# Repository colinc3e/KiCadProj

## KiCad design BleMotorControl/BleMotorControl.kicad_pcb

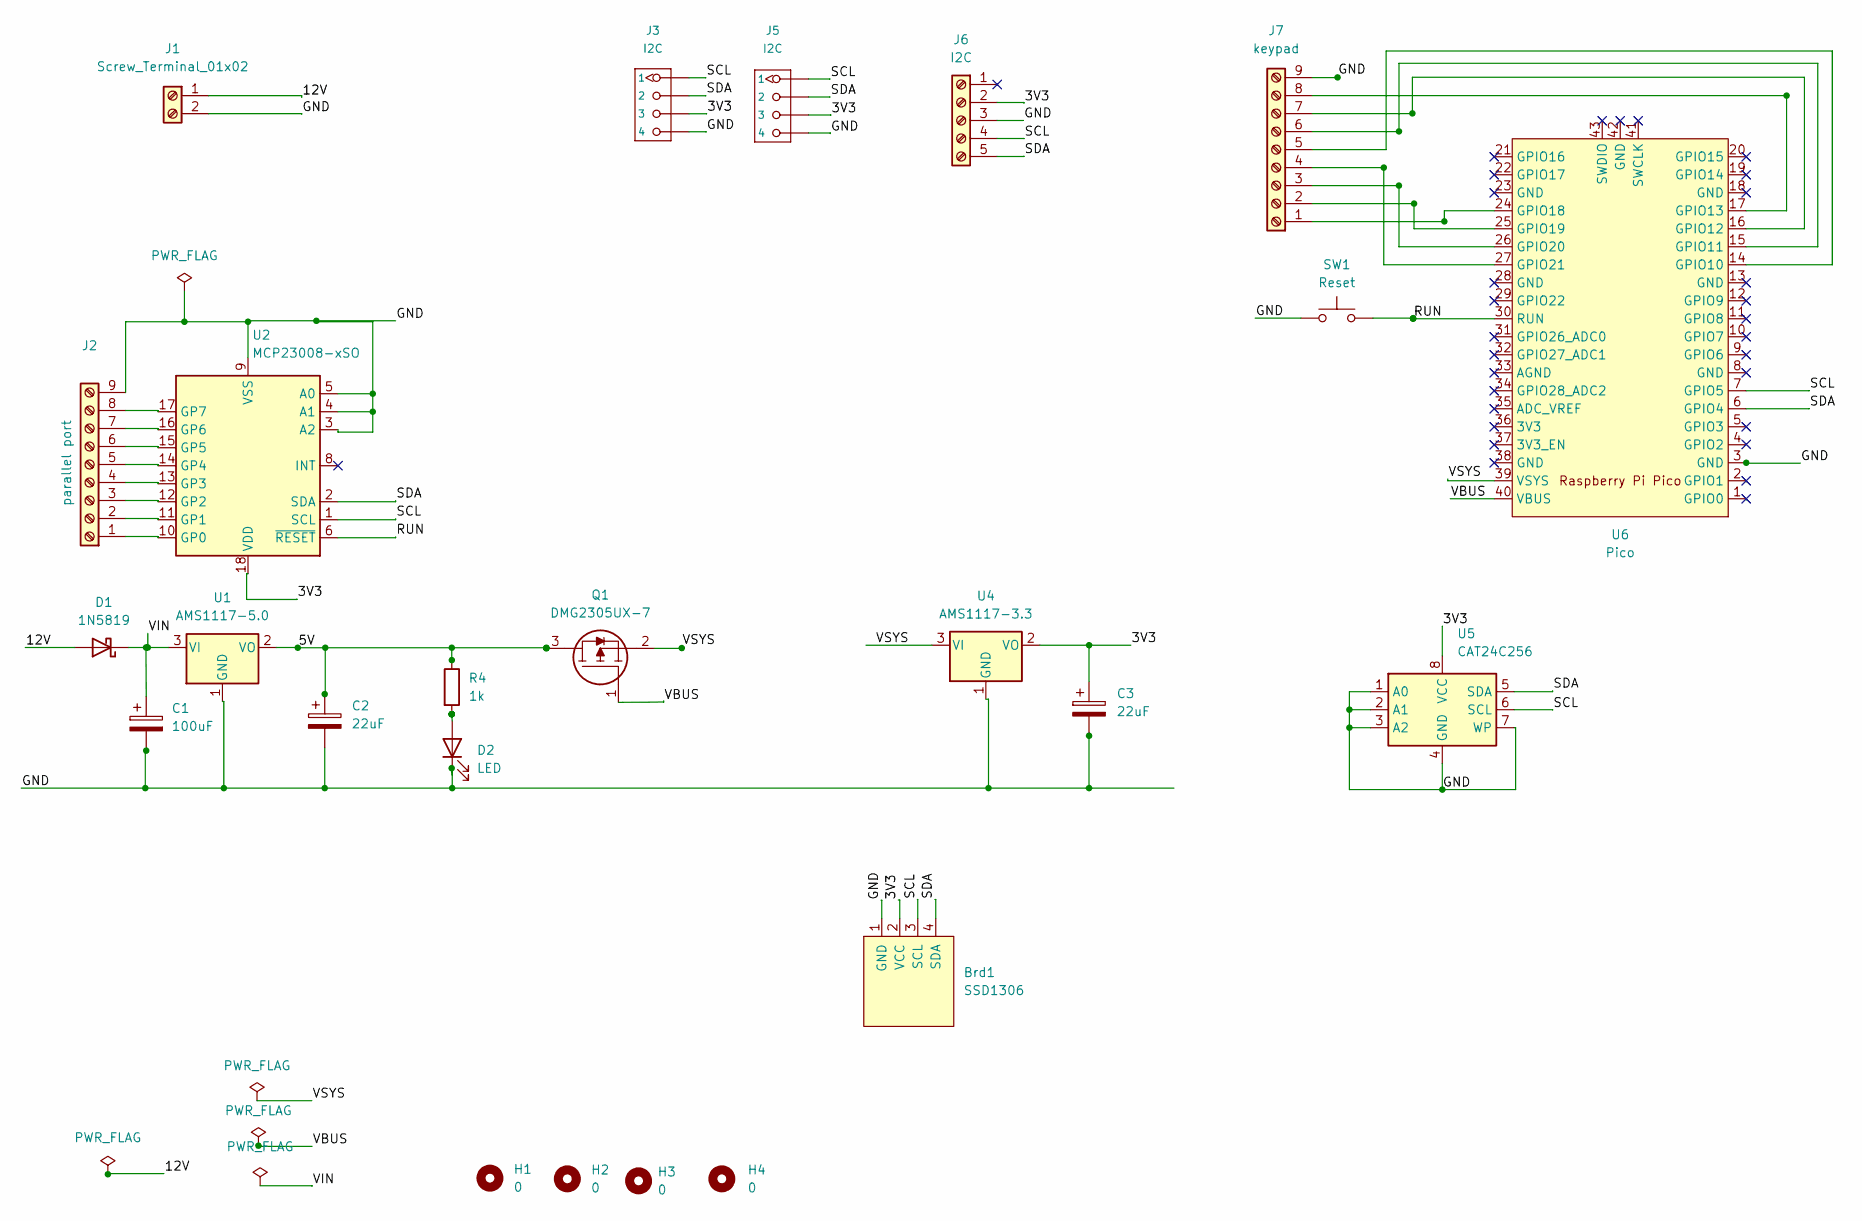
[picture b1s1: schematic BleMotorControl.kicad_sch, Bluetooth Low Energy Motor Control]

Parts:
Brd1: SSD1306; 128x64OLED
C1: 100uF; CP_Radial_Tantal_D8.0mm_P5.00mm
C2, C3: 22uF; CP_Radial_Tantal_D8.0mm_P5.00mm
D1: 1N5819; D_DO-41_SOD81_P10.16mm_Horizontal
D2: LED; LED_D3.0mm
H1, H2, H3, H4: 0; MountingHole_3.2mm_M3
J1: Screw_Terminal_01x02; TerminalBlock_Phoenix_PT-1,5-2-3.5-H_1x02_P3.50mm_Horizontal
J2: parallel port; PinHeader_1x09_P2.54mm_Vertical
J3, J5: I2C; HW4-2.0
J6: I2C; PinHeader_1x05_P2.54mm_Vertical
J7: keypad; PinHeader_1x09_P2.54mm_Vertical
Q1: DMG2305UX-7; SOT-23-3; Mouser Part Number 621-DMG2305UX-7
R4: 1k; R_1206_3216Metric
SW1: Reset; SW_Tactile_SPST_NO_Straight_CK_PTS636Sx25SMTRLFS
U1: AMS1117-5.0; SOT-223-3_TabPin2
U2: MCP23008-xSO; SOIC-18W_7.5x11.6mm_P1.27mm
U4: AMS1117-3.3; SOT-223-3_TabPin2
U5: CAT24C256; DIP-8_W7.62mm_LongPads
U6: Pico; RP2040Pico

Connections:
/3V3: Brd1.2 (VCC), C3.1, J3.3, J5.3, J6.2, U2.18 (VDD), U4.2 (VO), U5.8 (VCC)
/5V: C2.1, Q1.3, R4.1, U1.2 (VO)
/12V: D1.2 (A), J1.1
/GND: Brd1.1 (GND), C1.2, C2.2, C3.2, D2.1 (K), J1.2, J2.9, J3.4, J5.4, J6.3, J7.9, SW1.1, U1.1 (GND), U2.3 (A2), U2.4 (A1), U2.5 (A0), U2.9 (VSS), U4.1 (GND), U5.1 (A0), U5.2 (A1), U5.3 (A2), U5.4 (GND), U5.7 (WP), U6.3 (GND)
/RUN: SW1.2, U2.6 (~RESET), U6.30 (RUN)
/SCL: Brd1.3 (SCL), J3.1, J5.1, J6.4, U2.1 (SCL), U5.6 (SCL), U6.7 (GPIO5)
/SDA: Brd1.4 (SDA), J3.2, J5.2, J6.5, U2.2 (SDA), U5.5 (SDA), U6.6 (GPIO4)
/VBUS: Q1.1, U6.40 (VBUS)
/VIN: C1.1, D1.1 (K), U1.3 (VI)
/VSYS: Q1.2, U4.3 (VI), U6.39 (VSYS)
unnamed: D2.2 (A), R4.2
unnamed: J2.1, U2.10 (GP0)
unnamed: J2.2, U2.11 (GP1)
unnamed: J2.3, U2.12 (GP2)
unnamed: J2.4, U2.13 (GP3)
unnamed: J2.5, U2.14 (GP4)
unnamed: J2.6, U2.15 (GP5)
unnamed: J2.7, U2.16 (GP6)
unnamed: J2.8, U2.17 (GP7)
unnamed: J7.1, U6.24 (GPIO18)
unnamed: J7.2, U6.25 (GPIO19)
unnamed: J7.3, U6.26 (GPIO20)
unnamed: J7.4, U6.27 (GPIO21)
unnamed: J7.5, U6.14 (GPIO10)
unnamed: J7.6, U6.15 (GPIO11)
unnamed: J7.7, U6.16 (GPIO12)
unnamed: J7.8, U6.17 (GPIO13)

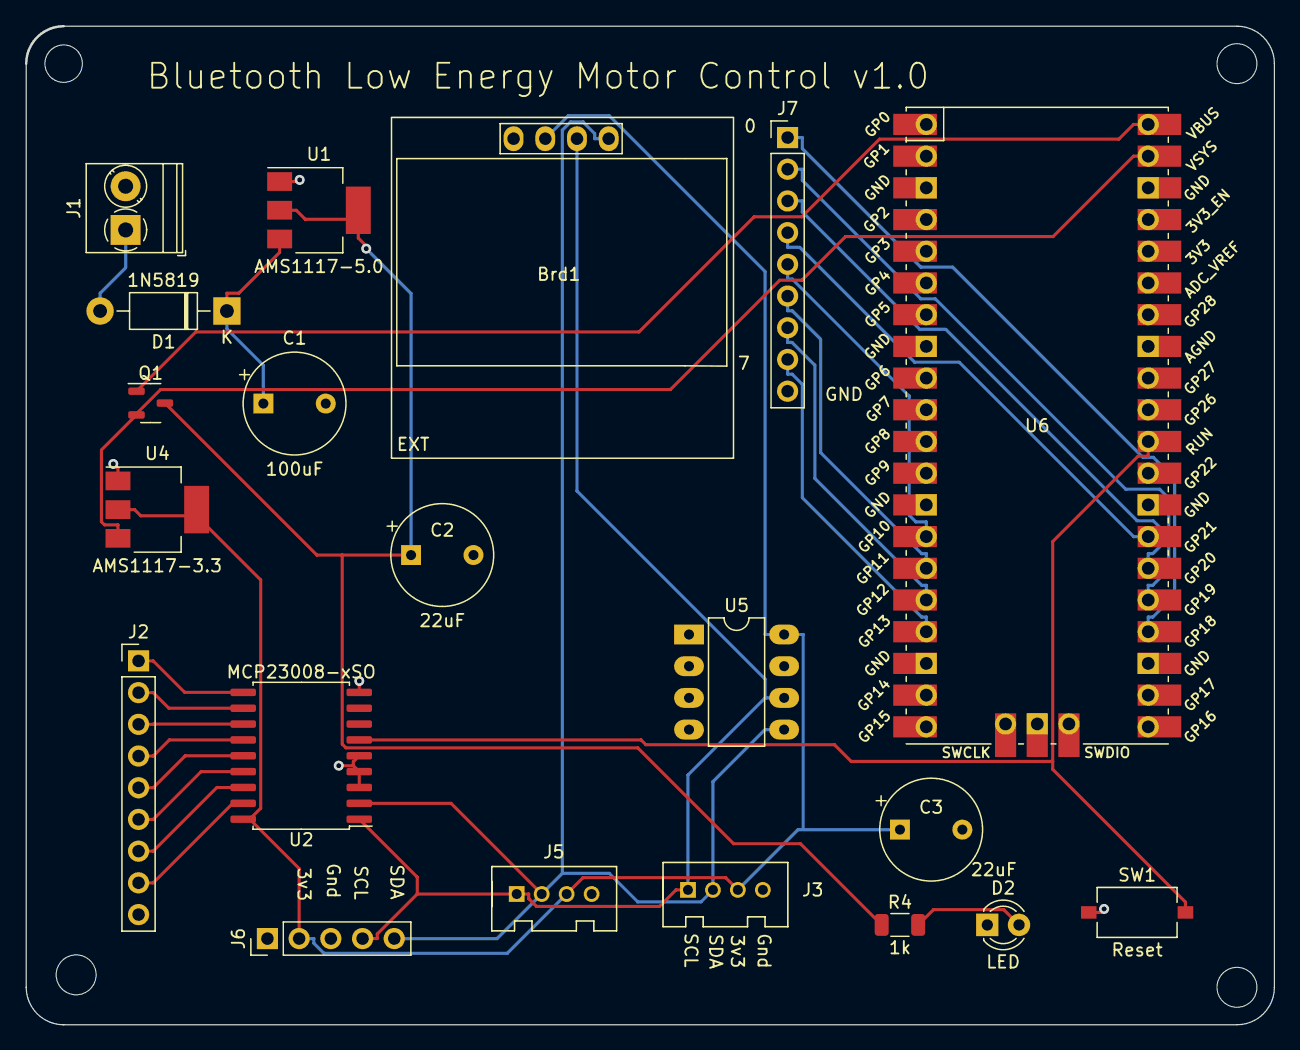
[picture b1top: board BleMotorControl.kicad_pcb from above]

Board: 2 copper layers, 100.0 x 80.0 mm, 24 parts (0 on the bottom side), 27 nets.

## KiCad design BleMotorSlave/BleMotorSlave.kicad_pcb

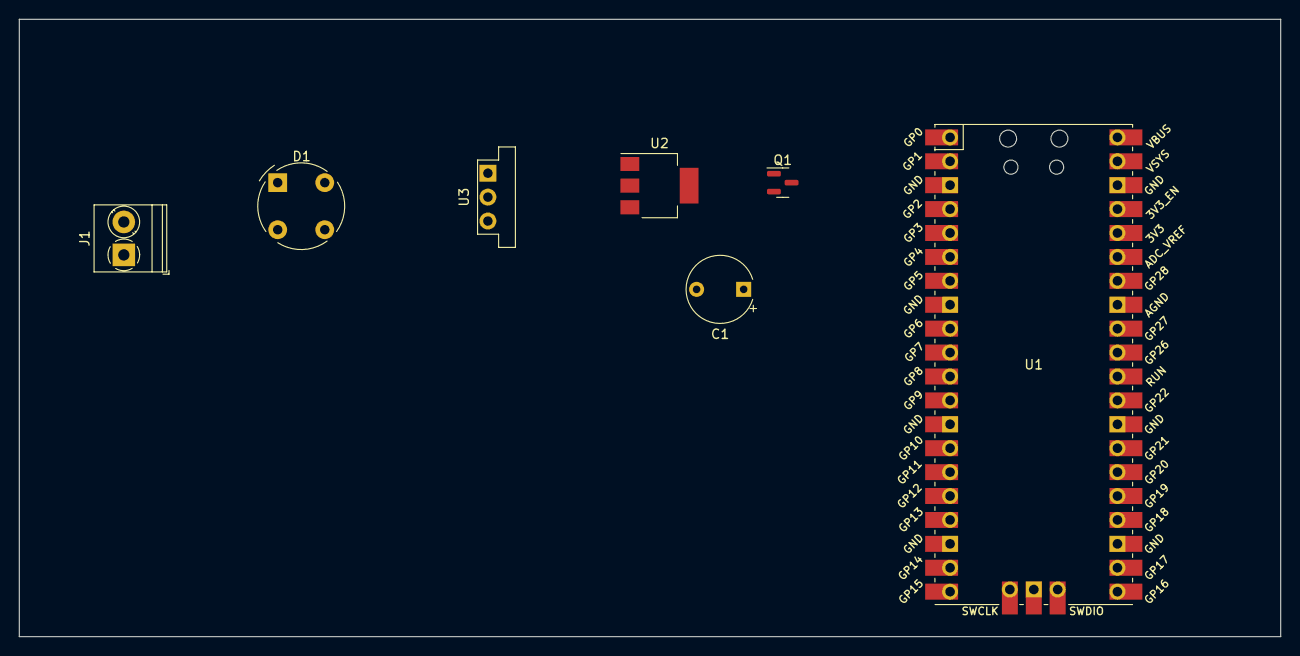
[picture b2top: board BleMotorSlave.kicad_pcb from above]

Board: 2 copper layers, 134.0 x 65.6 mm, 7 parts (0 on the bottom side), 8 nets, no tracks yet.

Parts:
C1: 22uF; CP_Radial_Tantal_D7.0mm_P5.00mm
D1: RB151; Diode_Bridge_Round_D9.0mm
J1: Screw_Terminal_01x02; TerminalBlock_Phoenix_PT-1,5-2-3.5-H_1x02_P3.50mm_Horizontal
Q1: DMG2305UX-7; SOT-23
U1: Pico; RPi_Pico_SMD_TH
U2: AMS1117-5.0; SOT-223-3_TabPin2
U3: OKI-78SR-12_1.0-W36-C; Converter_DCDC_Murata_OKI-78SR_Vertical

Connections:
/5V: C1.1, Q1.3, U2.2 (VO)
GND: C1.2, D1.3 (-), U2.1 (GND), U3.2 (GND)
unnamed: D1.1 (+), U3.1 (IN)
unnamed: D1.2, J1.2
unnamed: D1.4, J1.1
unnamed: Q1.1, U1.40 (VBUS)
unnamed: Q1.2, U1.39 (VSYS)
unnamed: U2.3 (VI), U3.3 (OUT)

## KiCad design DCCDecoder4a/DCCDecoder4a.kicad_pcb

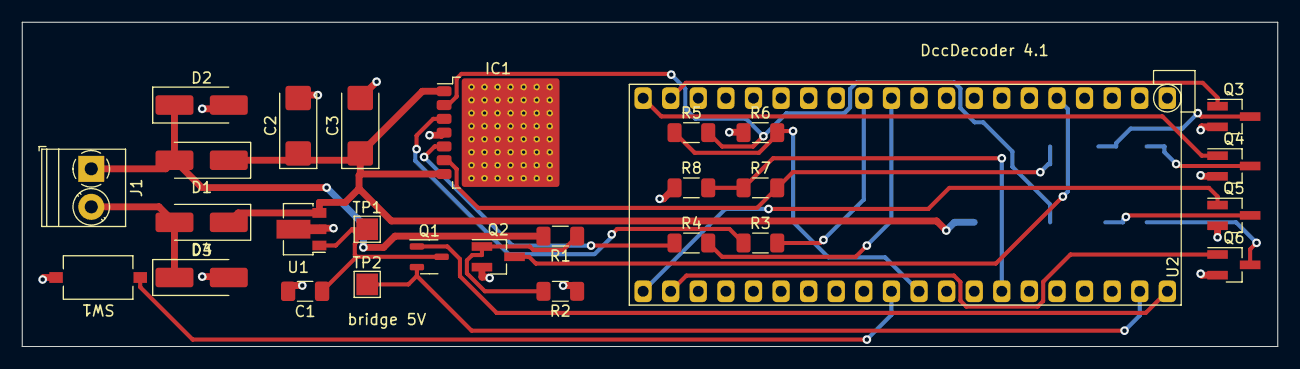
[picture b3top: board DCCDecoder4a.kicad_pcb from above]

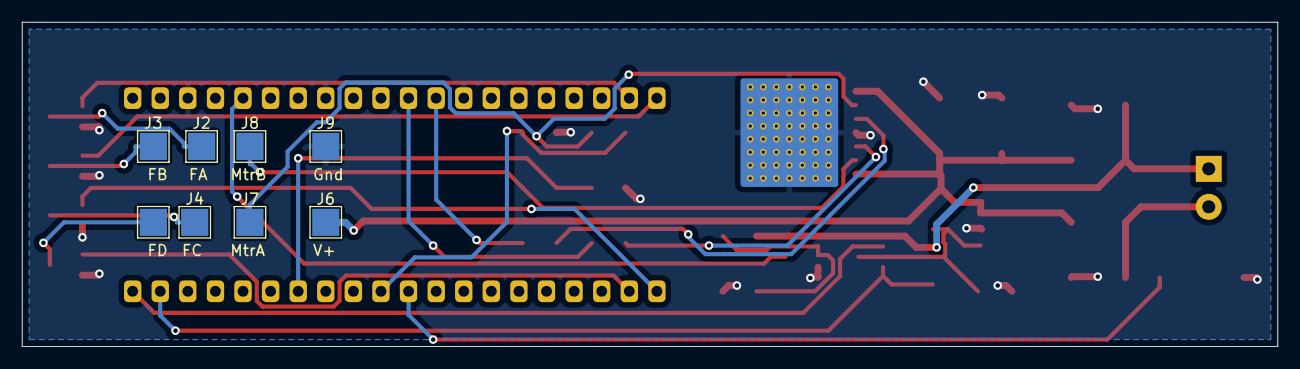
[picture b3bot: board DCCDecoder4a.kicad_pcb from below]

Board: 2 copper layers, 115.6 x 29.8 mm, 36 parts (8 on the bottom side), 26 nets.

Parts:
C1: 10uf/16V; C_1206_3216Metric_Pad1.33x1.80mm_HandSolder
C2: 10uF/25V; CP_EIA-6032-20_AVX-F_Pad2.25x2.35mm_HandSolder
C3: 10uF/25v; CP_EIA-6032-20_AVX-F_Pad2.25x2.35mm_HandSolder
D1, D2, D3, D4: RBR3L60AD; D_SMA_Handsoldering
IC1: BD62321HFP-TR; Rohm_HRP7
J1: Screw_Terminal_01x02; TerminalBlock_Phoenix_PT-1,5-2-3.5-H_1x02_P3.50mm_Horizontal
J2: 0; TestPoint_Pad_2.5x2.5mm
J3: 1; TestPoint_Pad_2.5x2.5mm
J4: 2; TestPoint_Pad_2.5x2.5mm
J5: 3; TestPoint_Pad_2.5x2.5mm
J6: +V; TestPoint_Pad_2.5x2.5mm
J7: M_OUT_B; TestPoint_Pad_2.5x2.5mm
J8: M_OUT_A; TestPoint_Pad_2.5x2.5mm
J9: GND; TestPoint_Pad_2.5x2.5mm
Q1: DMG2305UX-7; SOT-23-3
Q2, Q3, Q4, Q5, Q6: 2N7002BK; SOT-23_Handsoldering
R1, R2, R5, R7: 6k8; R_1206_3216Metric_Pad1.30x1.75mm_HandSolder
R3, R4: 10k; R_1206_3216Metric_Pad1.30x1.75mm_HandSolder
R6, R8: 1k; R_1206_3216Metric_Pad1.30x1.75mm_HandSolder
SW1: SW_Push; SW_Tactile_SPST_NO_Straight_CK_PTS636Sx25SMTRLFS
TP1, TP2: TestPoint; TestPoint_Pad_2.0x2.0mm
U1: AP7384-50Y; SOT-89-3
U2: Pico_RaspberryPico; RaspberryPico_TH_NoSWD

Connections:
+5V: C1.1, Q1.3, TP1.1, U1.1 (VO)
+V: C2.1, C3.1, D1.1 (K), D4.1 (K), IC1.1 (VCC_1), IC1.7 (VCC_2), J6.1, U1.3 (VI)
/ADC_EMF_A: R5.1, R6.2, U2.31 (GPIO26)
/DCC1: D1.2 (A), D2.1 (K), J1.1, R1.2
/DCC2: D3.1 (K), D4.2 (A), J1.2
/MOTOR_OUT_A: IC1.2 (OUT1), J7.1, R5.2
/MOTOR_OUT_B: IC1.6 (OUT2), J8.1, R7.2
/VSYS: Q1.2, TP2.1, U2.39 (VSYS)
ADC_EMF_B: R7.1, R8.2, U2.34 (GPIO28)
DCC_IN: Q2.3 (D), U2.5 (GPIO3)
FUNC_A: Q3.1 (G), U2.19 (GPIO14)
FUNC_B: Q4.1 (G), U2.20 (GPIO15)
FUNC_C: Q5.1 (G), U2.21 (GPIO16)
FUNC_D: Q6.1 (G), U2.22 (GPIO17)
GND: C1.2, C2.2, C3.2, D2.2 (A), D3.2 (A), IC1.4 (GND_1), J9.1, Q2.2 (S), Q3.2 (S), Q4.2 (S), Q5.2 (S), Q6.2 (S), R2.1, R6.1, R8.1, SW1.2, U1.2 (GND), U2.3 (GND), U2.8 (GND), U2.13 (GND)
unnamed: IC1.3 (FIN), R3.1
unnamed: IC1.5 (RIN), R4.1
unnamed: J2.1, Q3.3 (D)
unnamed: J3.1, Q4.3 (D)
unnamed: J4.1, Q5.3 (D)
unnamed: J5.1, Q6.3 (D)
unnamed: Q2.1 (G), R1.1, R2.2
unnamed: SW1.1, U2.30 (RUN)
unnamed: Q1.1, U2.40 (VBUS)
PWM_F: R3.2, U2.12 (GPIO9)
PWM_R: R4.2, U2.11 (GPIO8)

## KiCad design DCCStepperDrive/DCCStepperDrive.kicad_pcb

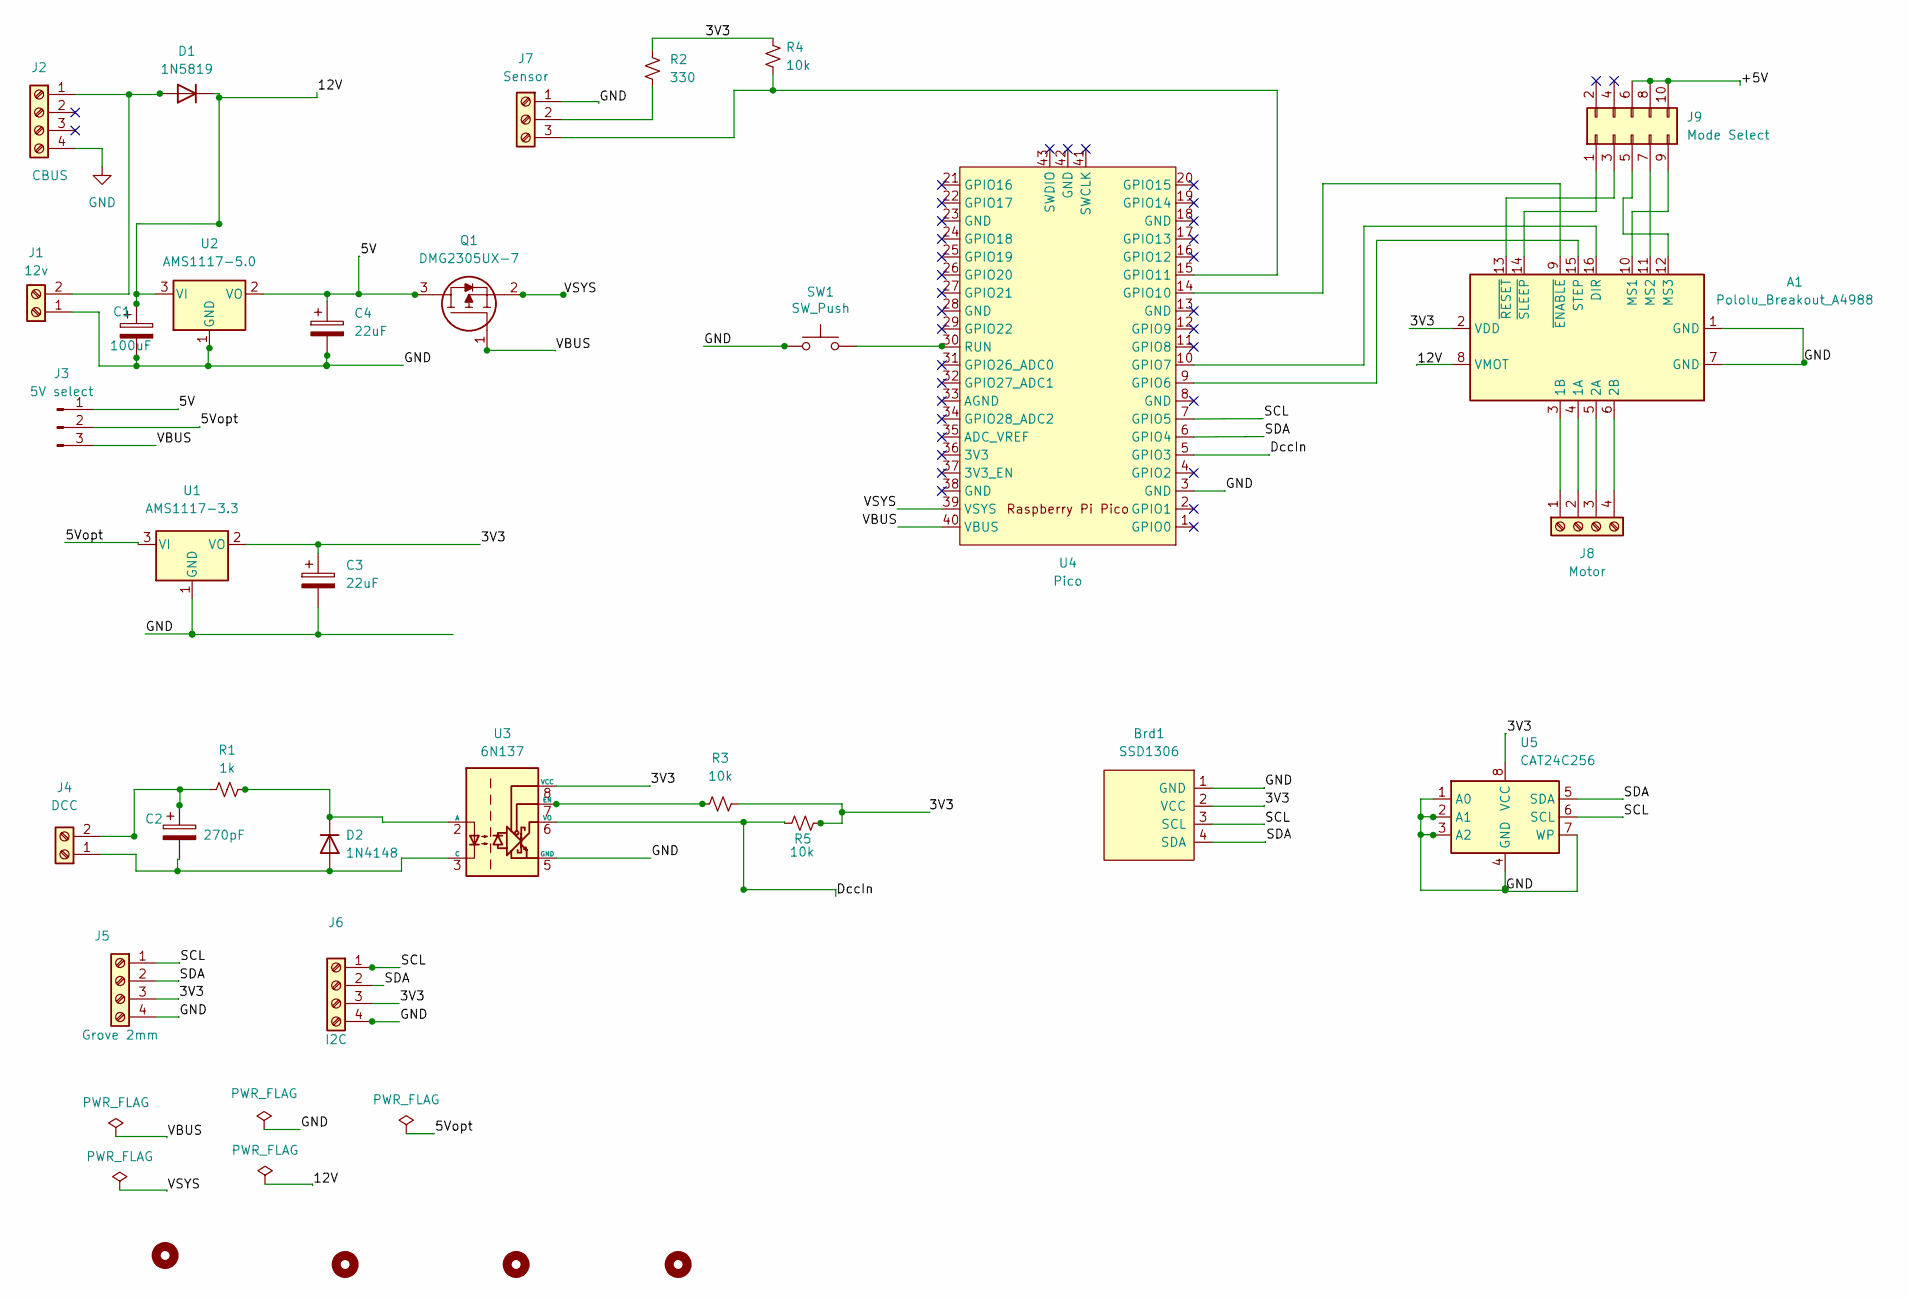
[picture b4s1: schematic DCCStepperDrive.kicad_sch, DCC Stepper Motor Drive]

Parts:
A1: Pololu_Breakout_A4988; Pololu_Breakout-16_15.2x20.3mm
Brd1: SSD1306; 128x64OLED
C1: 100uF; CP_Radial_D10.0mm_P7.50mm
C2: 270pF; CP_Radial_Tantal_D7.0mm_P5.00mm
C3, C4: 22uF; CP_Radial_Tantal_D7.0mm_P5.00mm
D1: 1N5819; D_DO-41_SOD81_P10.16mm_Horizontal
D2: 1N4148; D_DO-35_SOD27_P7.62mm_Horizontal
H1, H2, H3, H4: MountingHole; MountingHole_3.2mm_M3
J1: 12v; TerminalBlock_Phoenix_PT-1,5-2-3.5-H_1x02_P3.50mm_Horizontal
J2: CBUS; TerminalBlock_Phoenix_PT-1,5-4-3.5-H_1x04_P3.50mm_Horizontal
J3: 5V select; PinHeader_1x03_P2.54mm_Vertical
J4: DCC; TerminalBlock_Phoenix_PT-1,5-2-3.5-H_1x02_P3.50mm_Horizontal
J5: Grove 2mm; HW4-2.0
J6: I2C; HW4-2.0
J7: Sensor; TerminalBlock_Phoenix_PT-1,5-3-3.5-H_1x03_P3.50mm_Horizontal
J8: Motor; TerminalBlock_Phoenix_PT-1,5-4-3.5-H_1x04_P3.50mm_Horizontal
J9: Mode Select; PinHeader_2x05_P2.54mm_Vertical
Q1: DMG2305UX-7; SOT-23-3; Mouser Part Number 621-DMG2305UX-7
R1: 1k; R_1206_3216Metric
R2: 330; R_1206_3216Metric
R3, R4, R5: 10k; R_1206_3216Metric
SW1: SW_Push; SW_Tactile_SPST_NO_Straight_CK_PTS636Sx25SMTRLFS
U1: AMS1117-3.3; SOT-223-3_TabPin2
U2: AMS1117-5.0; SOT-223-3_TabPin2
U3: 6N137; DIP-8_W7.62mm
U4: Pico; RP2040Pico
U5: CAT24C256; DIP-8_W7.62mm_LongPads

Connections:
/3V3: A1.2 (VDD), Brd1.2 (VCC), C3.1, J5.3, J6.3, R2.2, R3.2, R4.2, R5.2, U1.2 (VO), U3.8 (VCC), U5.8 (VCC); also elsewhere on the board
/5V: C4.1, J3.1, Q1.3, U2.2 (VO)
/5Vopt: J3.2, U1.3 (VI)
/12V: A1.8 (VMOT), C1.1, D1.1 (K), U2.3 (VI)
/+5V: J9.6, J9.8, J9.10
/DccIn: R5.1, U3.6 (VO), U4.5 (GPIO3)
/SCL: Brd1.3 (SCL), J5.1, J6.1, U4.7 (GPIO5), U5.6 (SCL)
/SDA: Brd1.4 (SDA), J5.2, J6.2, U4.6 (GPIO4), U5.5 (SDA)
/VBUS: J3.3, Q1.1, U4.40 (VBUS)
/VSYS: Q1.2, U4.39 (VSYS)
GND: A1.1 (GND), A1.7 (GND), Brd1.1 (GND), C1.2, C3.2, C4.2, J1.1, J2.4, J5.4, J6.4, J7.1, SW1.1, U1.1 (GND), U2.1 (GND), U3.5 (GND), U4.3 (GND), U5.1 (A0), U5.2 (A1), U5.3 (A2), U5.4 (GND), U5.7 (WP); also elsewhere on the board
unnamed: A1.3 (1B), J8.1
unnamed: A1.4 (1A), J8.2
unnamed: A1.5 (2A), J8.3
unnamed: A1.6 (2B), J8.4
unnamed: A1.9 (~ENABLE), U4.14 (GPIO10)
unnamed: A1.10 (MS1), J9.9
unnamed: A1.11 (MS2), J9.7
unnamed: A1.12 (MS3), J9.5
unnamed: A1.13 (~RESET), J9.3
unnamed: A1.14 (~SLEEP), J9.1
unnamed: A1.15 (STEP), U4.9 (GPIO6)
unnamed: A1.16 (DIR), U4.10 (GPIO7)
unnamed: C2.1, J4.2, R1.1
unnamed: C2.2, D2.2 (A), J4.1, U3.3 (C)
unnamed: D1.2 (A), J1.2, J2.1
unnamed: D2.1 (K), R1.2, U3.2 (A)
unnamed: J7.2, R2.1
unnamed: J7.3, R4.1, U4.15 (GPIO11)
unnamed: R3.1, U3.7 (EN)
unnamed: SW1.2, U4.30 (RUN)

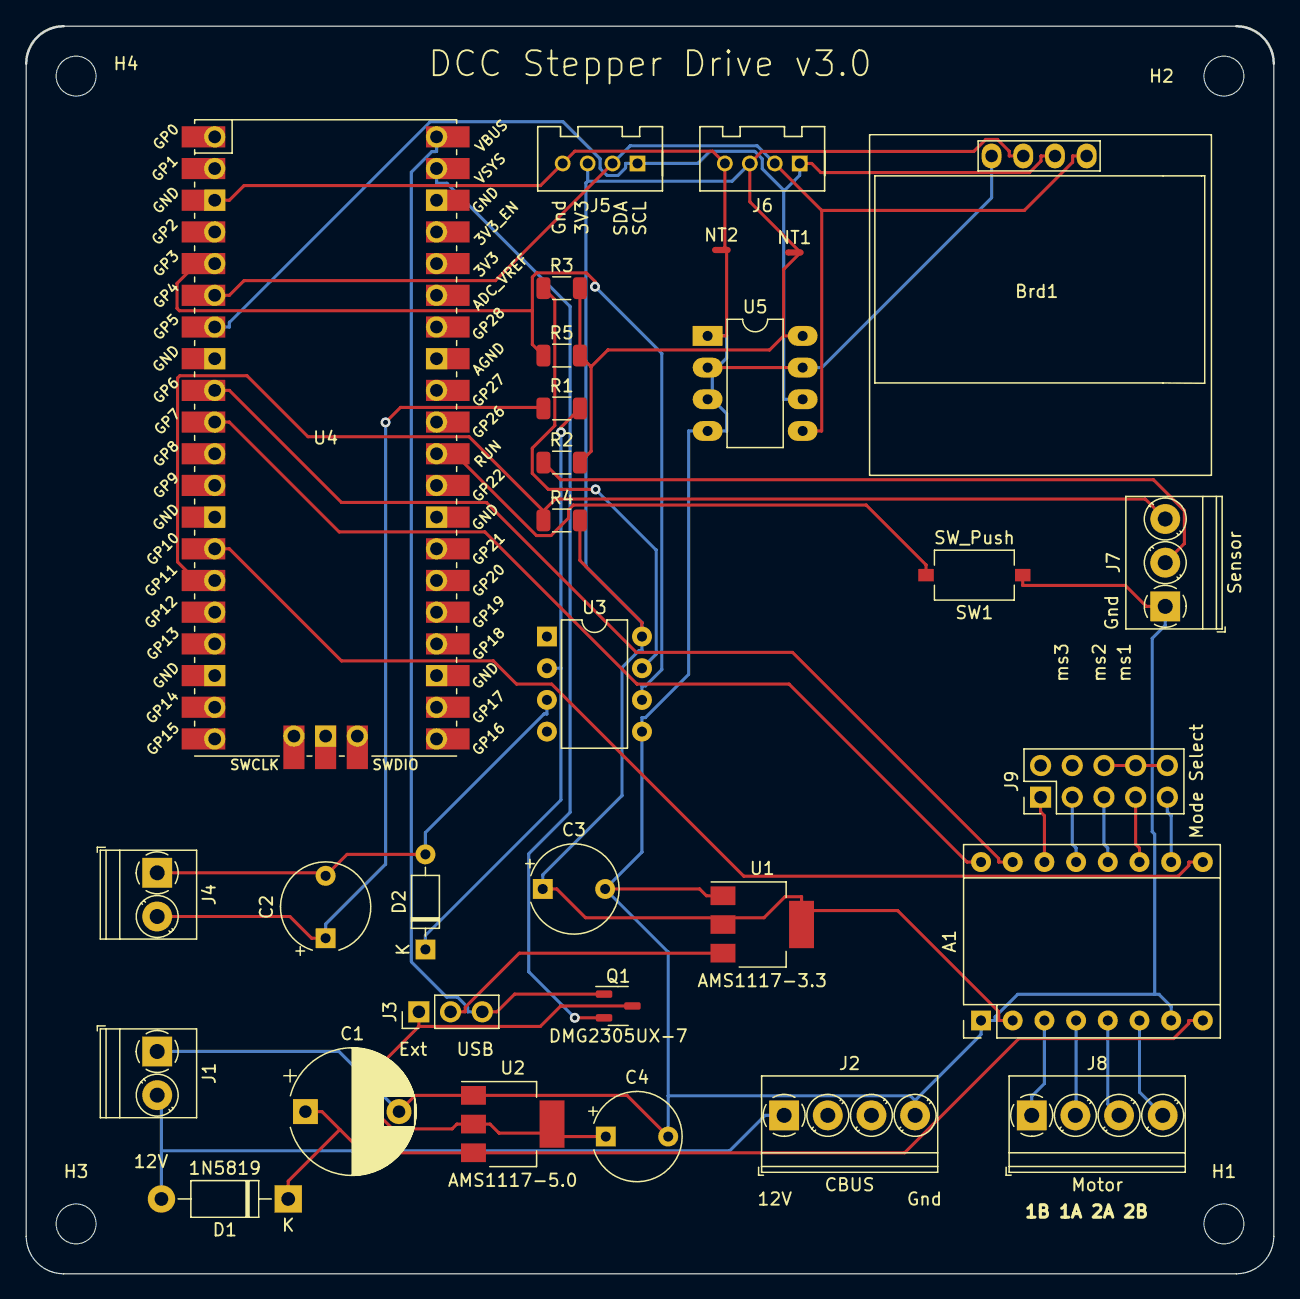
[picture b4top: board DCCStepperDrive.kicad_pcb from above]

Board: 2 copper layers, 100.0 x 100.0 mm, 35 parts (0 on the bottom side), 31 nets.

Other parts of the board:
NT1, NT2: NetTie_2; NetTie-2_SMD_Pad0.5mm

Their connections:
/3V3: NT1.2; also elsewhere on the board
GND: NT2.2; also elsewhere on the board

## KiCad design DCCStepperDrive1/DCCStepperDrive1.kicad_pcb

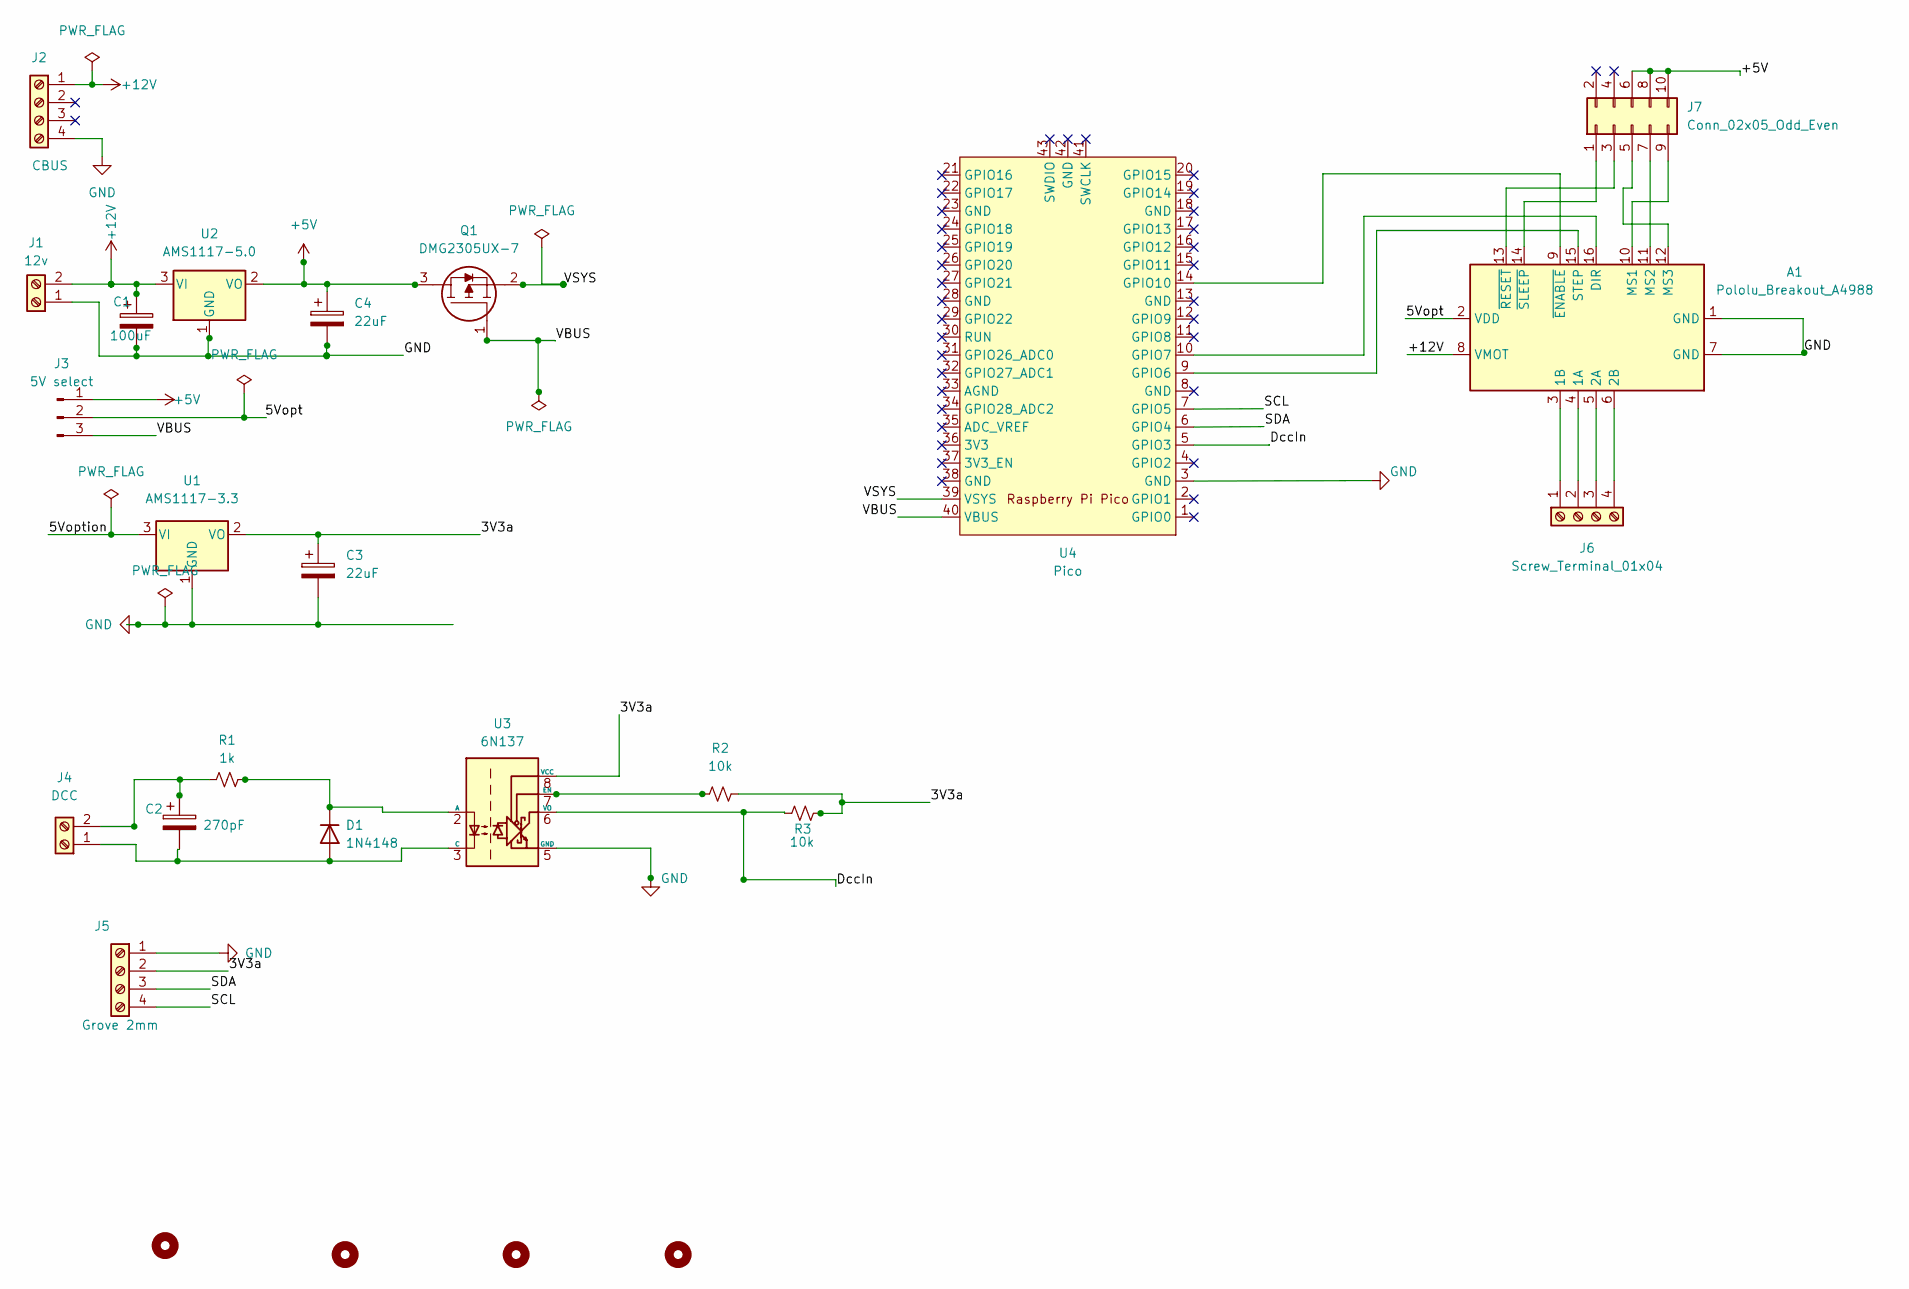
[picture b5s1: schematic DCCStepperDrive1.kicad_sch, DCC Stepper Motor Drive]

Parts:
A1: Pololu_Breakout_A4988; Pololu_Breakout-16_15.2x20.3mm
C1: 100uF; CP_Radial_D10.0mm_P7.50mm
C2: 270pF; CP_Radial_Tantal_D7.0mm_P5.00mm
C3, C4: 22uF; CP_Radial_Tantal_D7.0mm_P5.00mm
D1: 1N4148; D_DO-35_SOD27_P7.62mm_Horizontal
H1, H2, H3, H4: MountingHole; MountingHole_3.2mm_M3
J1: 12v; TerminalBlock_Phoenix_PT-1,5-2-5.0-H_1x02_P5.00mm_Horizontal
J2: CBUS; TerminalBlock_Phoenix_PT-1,5-4-3.5-H_1x04_P3.50mm_Horizontal
J3: 5V select; PinHeader_1x03_P2.54mm_Vertical
J4: DCC; TerminalBlock_Phoenix_PT-1,5-2-5.0-H_1x02_P5.00mm_Horizontal
J5: Grove 2mm; PinHeader_1x04_P2.00mm_Vertical
J6: Screw_Terminal_01x04; TerminalBlock_Phoenix_PT-1,5-4-3.5-H_1x04_P3.50mm_Horizontal
J7: Conn_02x05_Odd_Even; PinHeader_2x05_P2.54mm_Vertical
Q1: DMG2305UX-7; SOT-23-3; Mouser Part Number 621-DMG2305UX-7
R1: 1k; R_Axial_DIN0207_L6.3mm_D2.5mm_P10.16mm_Horizontal
R2, R3: 10k; R_Axial_DIN0207_L6.3mm_D2.5mm_P10.16mm_Horizontal
U1: AMS1117-3.3; SOT-223-3_TabPin2
U2: AMS1117-5.0; SOT-223-3_TabPin2
U3: 6N137; DIP-8_W7.62mm
U4: Pico; RPi_Pico_SMD_TH

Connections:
+5V: C4.1, J3.1, J7.6, J7.8, J7.10, Q1.3, U2.2 (VO)
+12V: A1.8 (VMOT), C1.1, J1.2, J2.1, U2.3 (VI)
/3V3a: C3.1, J5.2, R2.2, R3.2, U1.2 (VO), U3.8 (VCC)
/5Vopt: A1.2 (VDD), J3.2
/5Voption: U1.3 (VI)
/DccIn: R3.1, U3.6 (VO), U4.5 (GPIO3)
/SCL: J5.4, U4.7 (GPIO5)
/SDA: J5.3, U4.6 (GPIO4)
/VBUS: J3.3, Q1.1, U4.40 (VBUS)
/VSYS: Q1.2, U4.39 (VSYS)
GND: A1.1 (GND), A1.7 (GND), C1.2, C3.2, C4.2, J1.1, J2.4, J5.1, U1.1 (GND), U2.1 (GND), U3.5 (GND), U4.3 (GND)
unnamed: A1.3 (1B), J6.1
unnamed: A1.4 (1A), J6.2
unnamed: A1.5 (2A), J6.3
unnamed: A1.6 (2B), J6.4
unnamed: A1.9 (~ENABLE), U4.14 (GPIO10)
unnamed: A1.10 (MS1), J7.9
unnamed: A1.11 (MS2), J7.7
unnamed: A1.12 (MS3), J7.5
unnamed: A1.13 (~RESET), J7.3
unnamed: A1.14 (~SLEEP), J7.1
unnamed: A1.15 (STEP), U4.9 (GPIO6)
unnamed: A1.16 (DIR), U4.10 (GPIO7)
unnamed: D1.1 (K), R1.2, U3.2 (A)
unnamed: C2.2, D1.2 (A), J4.1, U3.3 (C)
unnamed: C2.1, J4.2, R1.1
unnamed: R2.1, U3.7 (EN)

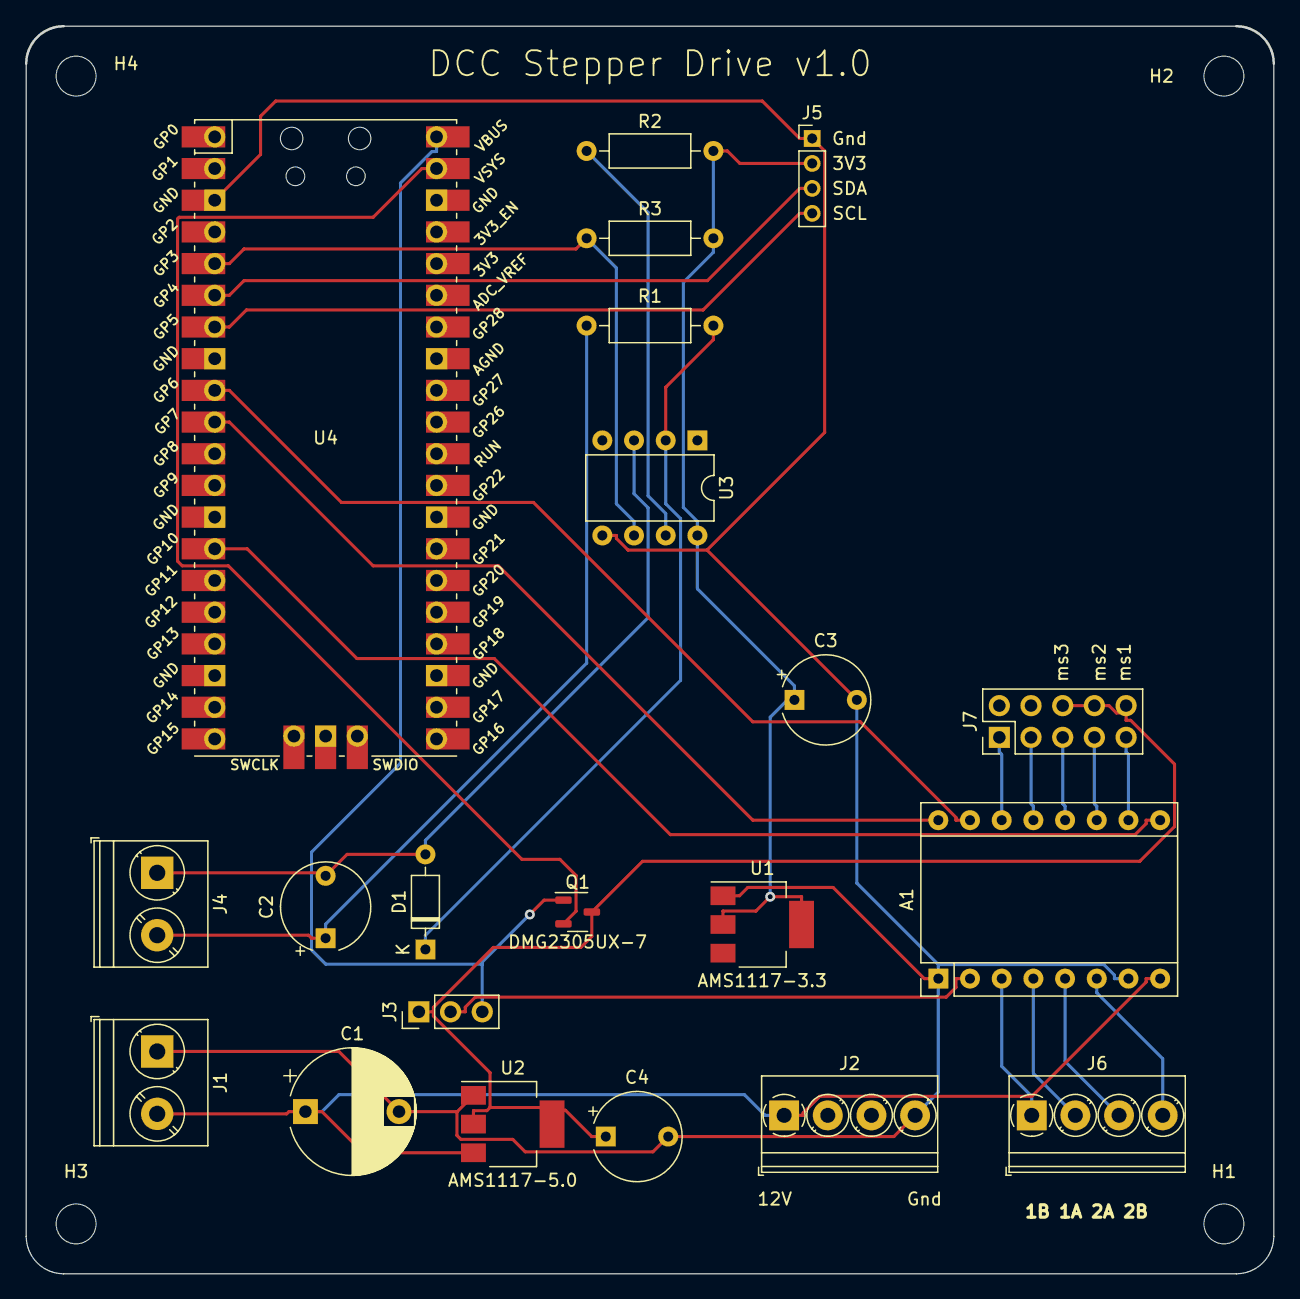
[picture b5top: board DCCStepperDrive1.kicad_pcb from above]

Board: 2 copper layers, 100.0 x 100.0 mm, 25 parts (0 on the bottom side), 26 nets.
